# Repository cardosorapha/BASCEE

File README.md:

# BASCEE

Este é um projeto de clone de Arduino utilizando o ATMega328P com duas memórias EEPROM e Calendário. O módulo disponibiliza saídas digitais, portas de comunicação I2C e serial, além de pinos para programação do microcontrolador. 

## Conexões

TODO: Colocar imagem do esquemático com breve descrição.

## Arquivos

O design principal, contido em "P03BASCEE.kicad_pcb" é de duas camadas com um plano de terra na camada inferior de cobre. Os arquivos "P03BASCEE_2Layers.kicad_pcb" e "P03BASCEE_4Layers.kicad_pcb" representam versões recém roteadas para duas e quatro camadas.

O arquivo "P03BASCEE.sch" contém o esquemático principal com uma página hierárquica, definida em "Connectors.sch", que contém os conectores do projeto.

Os esquemáticos de componentes utilizados no projeto estão contidos em "P03BASCEE-cache.lib", que pode ser carregado em qualquer instância de KiCAD sem que hajam esquemáticos nas bibliotecas globais ([como instalar bibliotecas não oficiais](https://kicad-pcb.org/libraries/third_party/)).

Os footprints de componentes utilizados no projeto estão contidos em "P03BASCEE.pretty", que pode ser carregado em qualquer instância de KiCAD sem que hajam footprints nas bibliotecas globais ([como instalar bibliotecas não oficiais](https://kicad-pcb.org/libraries/third_party/)).

## Roteamento

O roteamento dessa placa foi automático utilizando o [FreeRouting](https://freerouting.org/), que recebe arquivos exportados do KiCAD e realiza roteamentos minimizando o tamanho das camadas.

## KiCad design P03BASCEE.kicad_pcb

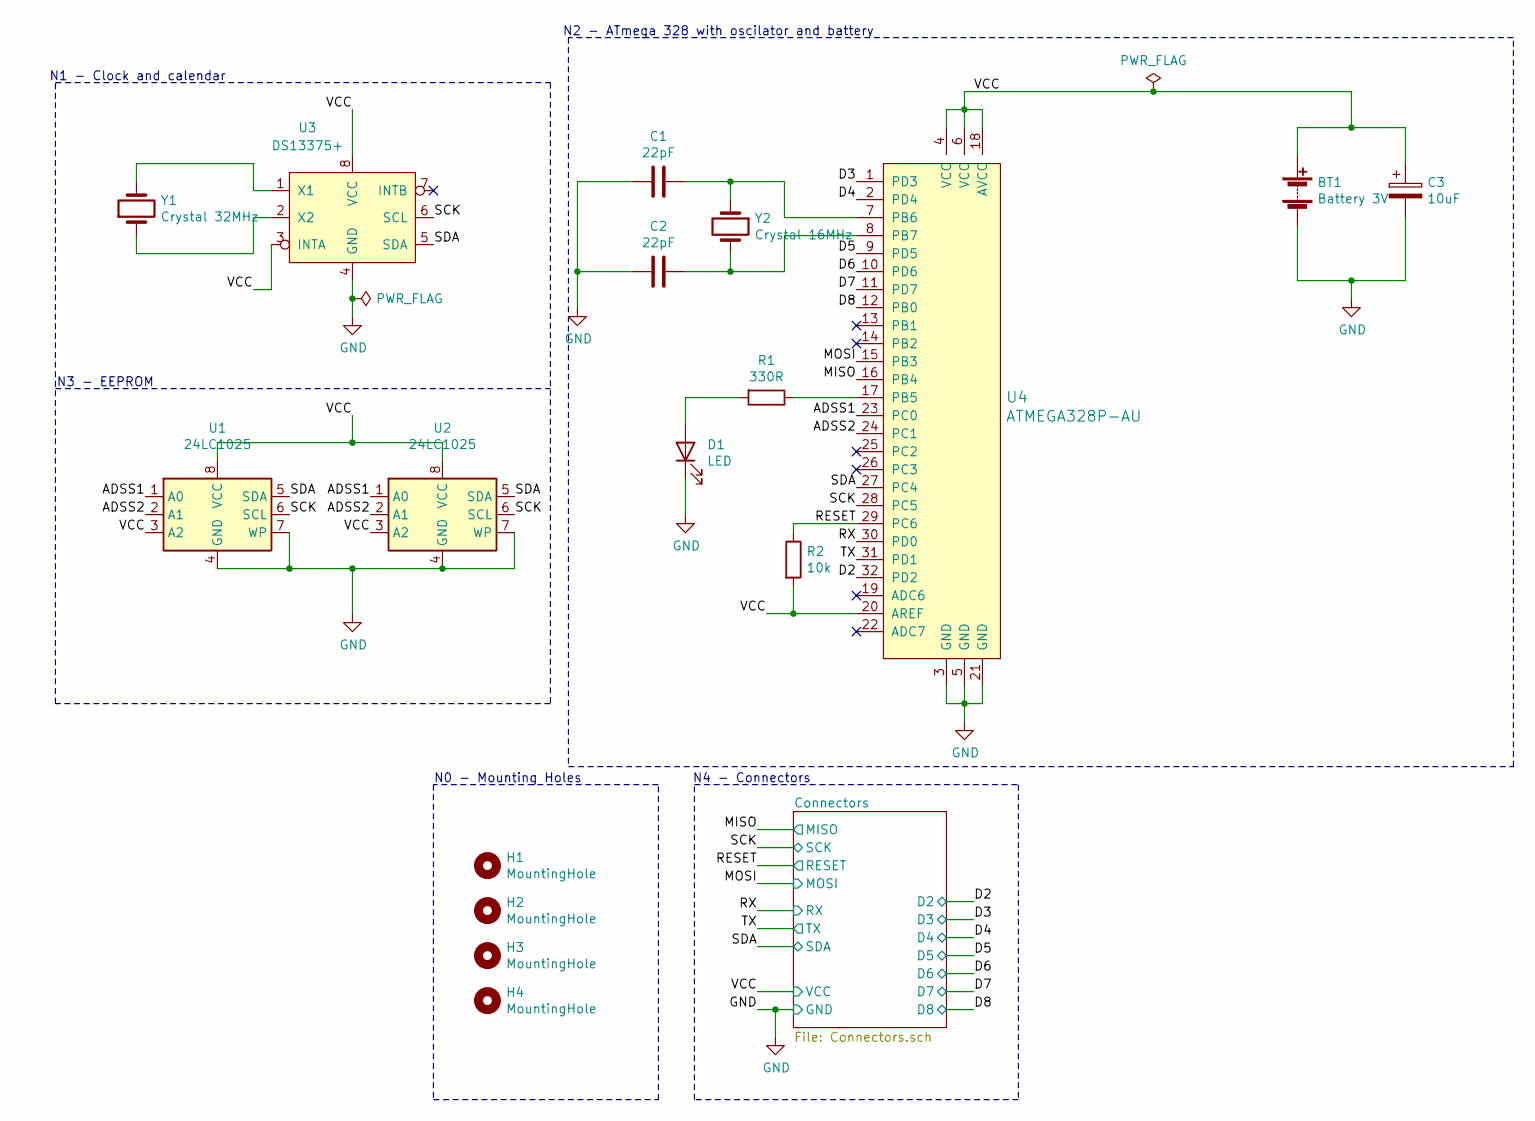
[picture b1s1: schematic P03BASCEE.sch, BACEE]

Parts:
BT1: Battery 3V; JST_PH_S2B-PH-K_1x02_P2.00mm_Horizontal
C1, C2: 22pF; C_0805_2012Metric
C3: 10uF; C_0805_2012Metric
D1: LED; LED_0805_2012Metric
H1, H2, H3, H4: MountingHole; MountingHole_2.2mm_M2_DIN965
R1: 330R; R_0805_2012Metric
R2: 10k; R_0805_2012Metric
U1, U2: 24LC1025; SO-8_5.3x6.2mm_P1.27mm
U3: DS13375+; SO-8_5.3x6.2mm_P1.27mm
U4: ATMEGA328P-AU; TQFP-32_7x7mm; MPN ATMEGA328P-AU; Digi-Key_PN ATMEGA328P-AU-ND
Y1: Crystal 32MHz; Crystal_SMD_MicroCrystal_CC7V-T1A-2Pin_3.2x1.5mm
Y2: Crystal 16MHz; Crystal_SMD_5032-2Pin_5.0x3.2mm_HandSoldering

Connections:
/ADSS1: U1.1 (A0), U2.1 (A0), U4.23 (PC0)
/ADSS2: U1.2 (A1), U2.2 (A1), U4.24 (PC1)
/D2: U4.32 (PD2); also elsewhere on the board
/D3: U4.1 (PD3); also elsewhere on the board
/D4: U4.2 (PD4); also elsewhere on the board
/D5: U4.9 (PD5); also elsewhere on the board
/D6: U4.10 (PD6); also elsewhere on the board
/D7: U4.11 (PD7); also elsewhere on the board
/D8: U4.12 (PB0); also elsewhere on the board
/MISO: U4.16 (PB4); also elsewhere on the board
/MOSI: U4.15 (PB3); also elsewhere on the board
/RESET: R2.1, U4.29 (PC6); also elsewhere on the board
/RX: U4.30 (PD0); also elsewhere on the board
/SCK: U1.6 (SCL), U2.6 (SCL), U3.6 (SCL), U4.28 (PC5); also elsewhere on the board
/SDA: U1.5 (SDA), U2.5 (SDA), U3.5 (SDA), U4.27 (PC4); also elsewhere on the board
/TX: U4.31 (PD1); also elsewhere on the board
/VCC: BT1.1 (+), C3.1, R2.2, U1.3 (A2), U1.8 (VCC), U2.3 (A2), U2.8 (VCC), U3.3 (INTA), U3.8 (VCC), U4.4 (VCC), U4.6 (VCC), U4.18 (AVCC), U4.20 (AREF); also elsewhere on the board
GND: BT1.2 (-), C1.2, C2.2, C3.2, D1.1 (K), U1.4 (GND), U1.7 (WP), U2.4 (GND), U2.7 (WP), U3.4 (GND), U4.3 (GND), U4.5 (GND), U4.21 (GND); also elsewhere on the board
unnamed: C1.1, U4.7 (PB6), Y2.1
unnamed: C2.1, U4.8 (PB7), Y2.2
unnamed: D1.2 (A), R1.2
unnamed: R1.1, U4.17 (PB5)
unnamed: U3.1 (X1), Y1.2
unnamed: U3.2 (X2), Y1.1

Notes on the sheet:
N1 - Clock and calendar
N3 - EEPROM
N2 - ATmega 328 with oscilator and battery
N4 - Connectors
N0 - Mounting Holes

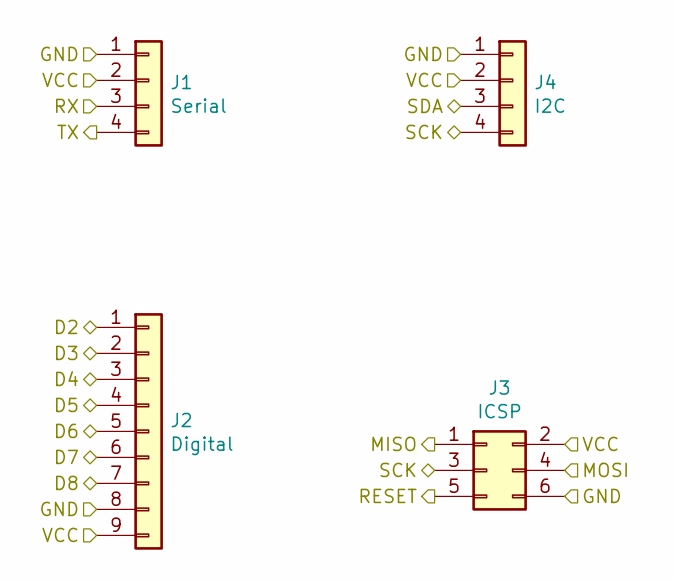
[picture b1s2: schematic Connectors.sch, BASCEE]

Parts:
J1: Serial; PinHeader_1x04_P2.54mm_Vertical
J2: Digital; PinHeader_1x09_P2.54mm_Vertical
J3: ICSP; PinHeader_2x03_P2.54mm_Vertical
J4: I2C; PinHeader_1x04_P2.54mm_Vertical

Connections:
/D2: J2.1; also elsewhere on the board
/D3: J2.2; also elsewhere on the board
/D4: J2.3; also elsewhere on the board
/D5: J2.4; also elsewhere on the board
/D6: J2.5; also elsewhere on the board
/D7: J2.6; also elsewhere on the board
/D8: J2.7; also elsewhere on the board
/MISO: J3.1; also elsewhere on the board
/MOSI: J3.4; also elsewhere on the board
/RESET: J3.5; also elsewhere on the board
/RX: J1.3; also elsewhere on the board
/SCK: J3.3, J4.4; also elsewhere on the board
/SDA: J4.3; also elsewhere on the board
/TX: J1.4; also elsewhere on the board
/VCC: J1.2, J2.9, J3.2, J4.2; also elsewhere on the board
GND: J1.1, J2.8, J3.6, J4.1; also elsewhere on the board

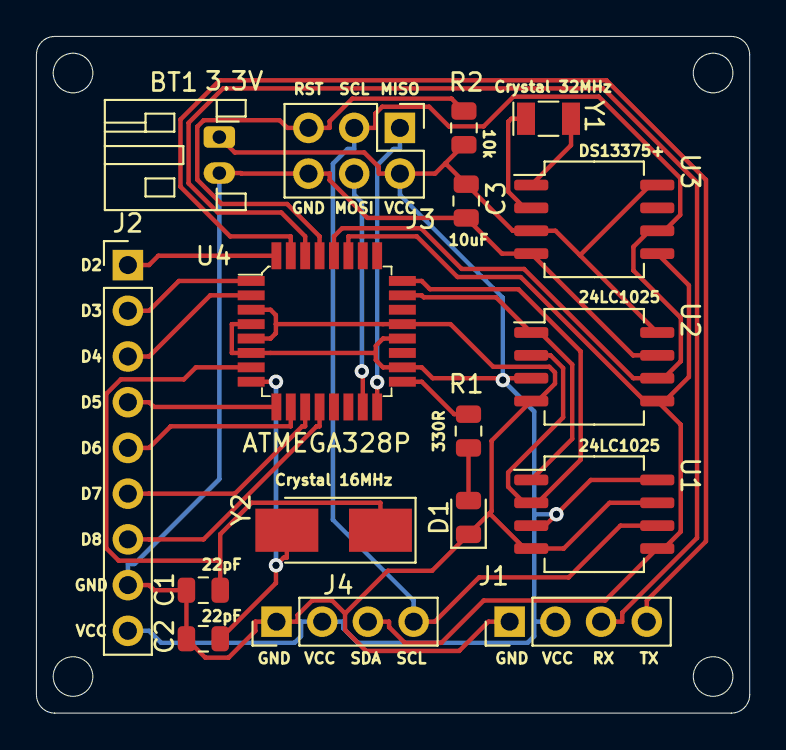
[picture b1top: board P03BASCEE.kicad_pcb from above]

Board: 2 copper layers, 39.6 x 37.6 mm, 21 parts (0 on the bottom side), 24 nets.

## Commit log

2020-06-28 Criação do repositório
2020-06-28 Adicionando README.md
2020-06-28 Configuração do bloco de título no esquemático
2020-06-28 Adicionados primeiros componentes disponíveis fora de páginas hierárquicas
2020-06-28 Criada página hierárquica para conectores
2020-06-28 Conectores colocados na página hierárquica correspondente
2020-06-28 Criado novo símbolo para CI e adicionado microcontrolador
2020-06-28 Adicionados cristais que faltavam
2020-06-28 Símbolos organizados
2020-06-28 Símbolos anotados
2020-06-28 Todos os valores e footprints adicionados
2020-06-28 Ligação dos conectores
2020-06-29 Feitas ligações entre componentes
2020-06-29 Esquemático completado e passou do DRC
2020-06-29 Descrições funcionais adicionadas
2020-06-29 NETLIST gerada
2020-06-29 Criado arquivo de PCB e corrigido título do esquemático
2020-06-29 Componentes colocados na PCB
2020-06-29 Furos de parafuso adicionados no esquemático e no PCB (boa prática)
2020-06-29 Componentes ajustados de forma compacta na PCB
2020-06-29 Criada borda da placa - sem espaço para buracos de montage
2020-06-29 Criada borda da placa - buracos de montagem reduzidos para 2.2mm e incluídos
2020-06-29 Roteamento concluído para duas camadas
2020-06-29 Roteamento concluído para duas camadas, adicionando arquivos restantes
2020-06-29 Roteamento para quatro camadas, projeto principal com duas
2020-06-29 Modificatos silkscreens para projeto duas camadas e adicionadas dimensões
2020-06-29 Removidos arquivos -bak
2020-06-29 Upload das bibliotecas locais
2020-07-03 Adicionada imagem 3D
